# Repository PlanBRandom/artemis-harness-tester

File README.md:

# Artemis Harness Tester

Production-grade 21-channel cable harness tester for SparkFun Artemis ATP fixtures.

## Features

- Auto-generated 21x21 connectivity matrix from a simple netlist
- Open, short, and crosstalk detection
- Per-channel resistance measurement with JSON output
- Profile-based limits for automated pass/fail checks
- Python CLI, live dashboard, and CSV viewer tools

## Quick Start

### Firmware

1. Open `firmware/harness_tester.ino` in Arduino IDE, or build from `platformio.ini`.
2. Install SparkFun Artemis board support.
3. Flash the firmware to the Artemis ATP.
4. Open a serial terminal at `115200` baud.

### PC tools

```bash
cd pc-tools
pip install -r requirements.txt
python tester_cli.py --port COM5 selftest
```

## Repository Layout

```text
firmware/      Firmware modules and entry points
pc-tools/      Python tools for CLI, dashboard, and CSV viewing
hardware/      KiCad design files, diagrams, and notes
profiles/      Example profile data
docs/          Assembly and validation notes
tests/         Basic test coverage
```

## Core Model

The tester is built around two source files:

- `firmware/channels.h`: channel index to physical pin mapping
- `firmware/nets.h`: channel index to expected net assignment

The firmware derives the expected matrix from `nets.h`, measures the actual matrix from hardware, then compares both to flag opens, shorts, and unexpected couplings.

## PC Tools

- `pc-tools/tester_cli.py`: command-line access to `MEASURE`, `MATRIX`, `PROFILE`, `SELFTEST`, and `CALIBRATE`
- `pc-tools/live_dashboard.py`: live serial console with matrix visualization
- `pc-tools/harness_viewer.py`: capture CSV matrix output from the serial stream
- `pc-tools/harness_gui.py`: simple CSV viewer
- `pc-tools/harness_web.py`: lightweight upload-and-view web UI

## Hardware Assets

- KiCad schematic: `hardware/kicad/artemis_harness_tester.kicad_sch`
- KiCad PCB: `hardware/kicad/artemis_harness_tester.kicad_pcb`
- Wiring diagram: `hardware/diagrams/ascii_wiring_diagram.txt`
- Validation notes: `WIRECHECK.md`

## Development Notes

- `AGENT.md` describes the safe extension boundaries for firmware and tools.
- `ARCHITECTURE.md` explains the modular firmware structure and command protocol.
- `QUICKSTART.md` covers bring-up, serial commands, and troubleshooting.

## License

MIT. See `LICENSE`.

MIT License (see LICENSE file)

---

## 🤖 AI Coding Agent Notes

This repo is structured to be AI-friendly:
- Modular headers
- Clear separation of concerns
- Predictable naming
- Explicit task list (see TASKS.md)
- Roadmap for future expansion (see ROADMAP.md)

Agents may safely:
- Add new test modules
- Extend PC tools
- Add GUIs or dashboards
- Add calibration routines
- Add new harness profiles

Agents should NOT:
- Modify `channels.h` or `nets.h` without explicit instruction
- Break the matrix API
- Remove CSV/JSON markers

---

## 📄 License

MIT License (see LICENSE file)

---

## 🤖 AI Coding Agent Notes

This repo is structured to be AI-friendly:
- Modular headers
- Clear separation of concerns
- Predictable naming
- Explicit task list (see TASKS.md)
- Roadmap for future expansion (see ROADMAP.md)

Agents may safely:
- Add new test modules
- Extend PC tools
- Add GUIs or dashboards
- Add calibration routines
- Add new harness profiles

Agents should NOT:
- Modify `channels.h` or `nets.h` without explicit instruction
- Break the matrix API
- Remove CSV/JSON markers

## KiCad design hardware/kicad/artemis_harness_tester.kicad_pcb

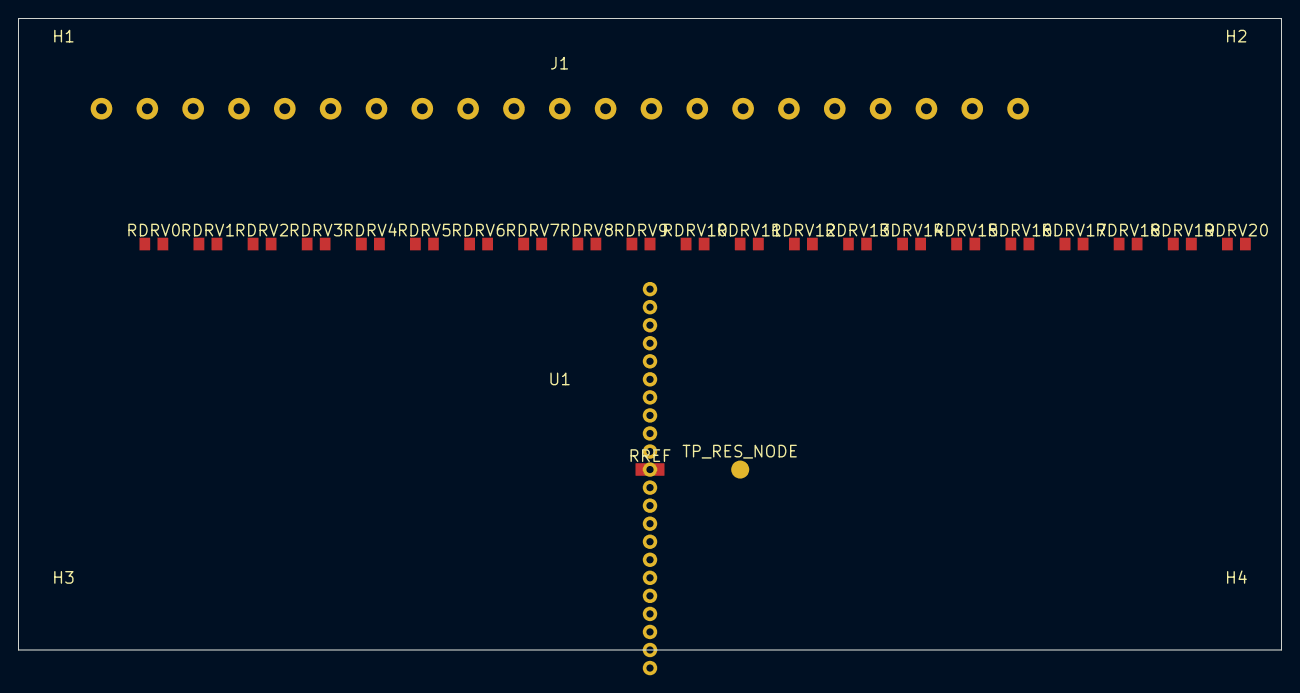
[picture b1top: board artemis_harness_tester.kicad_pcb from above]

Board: 2 copper layers, 140.0 x 70.0 mm, 29 parts (0 on the bottom side), 43 nets, no tracks yet.

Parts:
H1, H2, H3, H4: MOUNT; MountingHole_3.2mm
J1: Harness_21CH; TerminalBlock_1x21_P5.08mm
RDRV0, RDRV1, RDRV2, RDRV3, RDRV4, RDRV5, RDRV6, RDRV7, RDRV8, RDRV9, RDRV10, RDRV11, RDRV12, RDRV13, RDRV14, RDRV15, RDRV16, RDRV17, RDRV18, RDRV19, RDRV20: 1k; R_0805
RREF: 1k 1%; R_0805
TP_RES_NODE: RES_NODE; SMD_Pad
U1: Artemis_ATP

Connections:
CH0: J1.1, RDRV0.1
CH1: J1.2, RDRV1.1
CH2: J1.3, RDRV2.1
CH3: J1.4, RDRV3.1
CH4: J1.5, RDRV4.1
CH5: J1.6, RDRV5.1
CH6: J1.7, RDRV6.1
CH7: J1.8, RDRV7.1
CH8: J1.9, RDRV8.1
CH9: J1.10, RDRV9.1
CH10: J1.11, RDRV10.1
CH11: J1.12, RDRV11.1
CH12: J1.13, RDRV12.1
CH13: J1.14, RDRV13.1
CH14: J1.15, RDRV14.1
CH15: J1.16, RDRV15.1
CH16: J1.17, RDRV16.1
CH17: J1.18, RDRV17.1
CH18: J1.19, RDRV18.1
CH19: J1.20, RDRV19.1
CH20: J1.21, RDRV20.1
RES_DRIVE: RREF.1, U1.23
U1_PIN2: RDRV0.2, RREF.2, TP_RES_NODE.1, U1.2
U1_PIN3: RDRV1.2, U1.3
U1_PIN4: RDRV2.2, U1.4
U1_PIN5: RDRV3.2, U1.5
U1_PIN6: RDRV4.2, U1.6
U1_PIN7: RDRV5.2, U1.7
U1_PIN8: RDRV6.2, U1.8
U1_PIN9: RDRV7.2, U1.9
U1_PIN10: RDRV8.2, U1.10
U1_PIN11: RDRV9.2, U1.11
U1_PIN12: RDRV10.2, U1.12
U1_PIN13: RDRV11.2, U1.13
U1_PIN14: RDRV12.2, U1.14
U1_PIN15: RDRV13.2, U1.15
U1_PIN16: RDRV14.2, U1.16
U1_PIN17: RDRV15.2, U1.17
U1_PIN18: RDRV16.2, U1.18
U1_PIN19: RDRV17.2, U1.19
U1_PIN20: RDRV18.2, U1.20
U1_PIN21: RDRV19.2, U1.21
U1_PIN22: RDRV20.2, U1.22

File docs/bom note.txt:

ARTEMIS HARNESS TESTER - KICAD NETLIST STUB (CHANNELS + CAT5)
==========================================================

Net Naming Convention
---------------------
- CH0..CH20: Logical channel nets between Artemis and series resistors.
- J1_x: Harness connector pins.
- CAT5_A_x, CAT5_B_x, CAT5_C_x: Individual CAT5 conductors.

Example Nets
------------
(net "CH0")
(net "CH1")
...
(net "CH20")

(net "J1_1")
(net "J1_2")
...
(net "J1_21")

(net "CAT5_A_WO")   ; Cable A, White/Orange
(net "CAT5_A_O")    ; Cable A, Orange
(net "CAT5_A_WG")   ; Cable A, White/Green
(net "CAT5_A_G")    ; Cable A, Green
(net "CAT5_A_WB")   ; Cable A, White/Blue
(net "CAT5_A_B")    ; Cable A, Blue
(net "CAT5_A_WBr")  ; Cable A, White/Brown
(net "CAT5_A_Br")   ; Cable A, Brown

(similar for CAT5_B_* and CAT5_C_*)

Logical Connections (Conceptual)
--------------------------------
CH0   ↔ RDRV0 ↔ J1_1 ↔ CAT5_A_WO
CH1   ↔ RDRV1 ↔ J1_2 ↔ CAT5_A_O
CH2   ↔ RDRV2 ↔ J1_3 ↔ CAT5_A_WG
CH3   ↔ RDRV3 ↔ J1_4 ↔ CAT5_A_G
CH4   ↔ RDRV4 ↔ J1_5 ↔ CAT5_A_WB
CH5   ↔ RDRV5 ↔ J1_6 ↔ CAT5_A_B
CH6   ↔ RDRV6 ↔ J1_7 ↔ CAT5_A_WBr
CH7   ↔ RDRV7 ↔ J1_8 ↔ CAT5_A_Br

CH8   ↔ RDRV8  ↔ J1_9  ↔ CAT5_B_WO
CH9   ↔ RDRV9  ↔ J1_10 ↔ CAT5_B_O
CH10  ↔ RDRV10 ↔ J1_11 ↔ CAT5_B_WG
CH11  ↔ RDRV11 ↔ J1_12 ↔ CAT5_B_G
CH12  ↔ RDRV12 ↔ J1_13 ↔ CAT5_B_WB
CH13  ↔ RDRV13 ↔ J1_14 ↔ CAT5_B_B
CH14  ↔ RDRV14 ↔ J1_15 ↔ CAT5_B_WBr
CH15  ↔ RDRV15 ↔ J1_16 ↔ CAT5_B_Br

CH16  ↔ RDRV16 ↔ J1_17 ↔ CAT5_C_WO
CH17  ↔ RDRV17 ↔ J1_18 ↔ CAT5_C_O
CH18  ↔ RDRV18 ↔ J1_19 ↔ CAT5_C_WG
CH19  ↔ RDRV19 ↔ J1_20 ↔ CAT5_C_G
CH20  ↔ RDRV20 ↔ J1_21 ↔ CAT5_C_WB

Bill of Materials Note
----------------------
- RDRV0–RDRV20:
  - Quantity: 21
  - Description: Series resistor, 1,000 ohms, 1% tolerance, 1/4 W (or as per design)
  - Purpose: Channel isolation and current limiting between Artemis pins and harness.
- RREF:
  - Quantity: 1
  - Description: Precision reference resistor, 1,000 ohms, 0.1–0.5% tolerance recommended.
  - Purpose: Defines measurement current and accuracy for resistance measurements.
- LED_IND:
  - Quantity: 1
  - Description: Indicator LED, any color, with matching current-limiting resistor.
  - Purpose: Visual indication of measurement activity on the resistance drive signal.
- CAT5 Cables:
  - Quantity: 3
  - Description: CAT5 or CAT5e cable, 4 twisted pairs, TIA-568B color code.
  - Purpose: Harness wiring for channels CH0–CH20 and spare conductors.

This stub can be adapted into a full KiCad schematic/netlist by assigning these net names to symbols and connectors in the project.

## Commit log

2025-12-22 Initial commit - Complete harness tester with firmware, docs, and tools
2026-04-06 Migrate current project and normalize naming
